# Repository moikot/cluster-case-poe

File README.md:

# A quiet case for three Raspberry Pis

* ✨Power over Ethernet
* ✨Hot-swap support 
* ✨PWM fans support
---

## Table of Contents

- [Enclosure](#enclosure)
  - [Power and I2C rail](#power-and-i2c-rail)
  - [Fan controller](#fan-controller)
  - [Bill of materials](#enclosure-bill-of-materials)
- [Frames](#frames)
  - [PoE assembly](#poe-assembly)
  - [Bill of materials](#frames-bill-of-materials)
- [Other hardware needed](#other-hardware-needed)
- [License](#license)

## Enclosure

The case box is built from the following parts ([drawings](drawings/cluster-box-drawings.pdf)):

* Left, right, top, and bottom panels.
* Top and bottom panels with grooves for the Raspberry Pi frames.
* A back panel with a fan grill for 80mm x 80mm fan.
* A front panel with openings for USB and Ethernet ports. 

> Watch this [video](https://youtu.be/zfYN2NjLpm8) to see how to assembly the case.

### Power and I2C rail

The power and I2C rail connects all Raspberry Pis to the I2C bus and provides power to the fan controller and a chassis fan. Low forward drop Schottky diodes combined in an OR-ing circuit provide power to the load when at least one Raspberry Pi is installed without the risk of reverse current flow. 

> * [Schematics and PCB (EagleCAD)](power-rail)
> * [BOM](power-rail/power-rail-bom.csv)

### Fan controller

The fan controller converts 5V to 12V and uses [EMC2101-R IC](https://www.microchip.com/wwwproducts/en/EMC2101) from Microchip/SMSC to control a 4-pin PWM fan and monitor its speed via the I2C bus. This controller is installed on the left panel of the enclosure and connected to the [Power and I2C rail](#power-and-i2c-rail).

> * [Schematics and PCB (EagleCAD)](fan-controller)
> * [BOM](fan-controller/fan-controller-bom.csv)

### Bill of materials

|        Part         | Quantity | Link |
|---------------------|----------|------|
| M2.5 x 14mm screw   | 3        | [M2.5 machine screws nuts kit](https://www.ebay.com/itm/182282169506)     |
| M2.5 x 10mm screw   | 1        | [M2.5 machine screws nuts kit](https://www.ebay.com/itm/182282169506)     |
| M2.5 nut            | 4        | [M2.5 machine screws nuts kit](https://www.ebay.com/itm/182282169506)     |
| M2.5 x 2mm spacer   | 4        | [M2.5 round plastic spacer](https://www.digikey.com/en/products/detail/w%C3%BCrth-elektronik/960020021/9488359)     |
| M3 x 12mm screw     | 8        | 	[M3x12mm machine screws](https://www.amazon.com/Uxcell-a15070200ux0058-Stainless-Phillips-Screws/dp/B012TE1TBS) |
| M3 nut              | 8        | [M3 hexagon nuts](https://www.amazon.com/uxcell-Metric-Stainless-Hexagon-Silver/dp/B07H3T4859) |
| M3 nylon washer     | 8        | [M3 nylon flat washers](https://www.amazon.com/uxcell-Insulation-Spacer-Washer-Gasket/dp/B016EPLM5G) |
| M4 x 14mm screw     | 4        | [M4x14mm machine screws](https://www.amazon.com/uxcell-M4x14mm-Phillips-Stainless-Fasteners/dp/B07MF44LGC) |
| M4 nut              | 4        | [M4 hexagon nuts](https://www.amazon.com/uxcell-Metric-Stainless-Hexagon-Silver/dp/B07H3VF3BF) |
| 80mm x 80mm x 25mm fan | 1        | [Noctua NF-A8 PWM](https://noctua.at/en/nf-a8-pwm) |
| Power and I2C rail | 1        | [Schematics and PCB (EagleCAD)](power-rail), [BOM](power-rail/power-rail-bom.csv) |
| Fan controller | 1        | [Schematics and PCB (EagleCAD)](fan-controller), [BOM](fan-controller/fan-controller-bom.csv) |
| Case panels | 8        | [Drawings](drawings/cluster-box-drawings.pdf), [Templates for laser cutting](drawings/cluster-box-laser-cut.pdf) |

## Frames

Raspberry Pis need to be mounted on frames so that they can be pushed into the case and retracted individually ([drawings](drawings/frame-drawings.pdf)).

### PoE assembly

The solution relies on a custom PoE HAT with [RT5400-5V 30W module](https://www.aliexpress.com/item/33038562052.html). For this HAT to work, the switch your cluster is connected to needs to support IEEE 802.3af Power over Ethernet protocol (e.g. [TL-SG1005P switch](https://www.tp-link.com/us/business-networking/poe-switch/tl-sg1005p/)). 

> * [Schematics and PCB (EagleCAD)](poe-assembly)
> * [BOM](poe-assembly/poe-assembly-bom.csv)

### Bill of materials
|        Part         | Quantity | Link |
|---------------------|----------|------|
| M2.5 x 10mm screw   | 12       | [M2.5 machine screws nuts kit](https://www.ebay.com/itm/182282169506)     |
| M2.5 x 5mm screw    | 6        | [M2.5 machine screws nuts kit](https://www.ebay.com/itm/182282169506)     |
| M2.5 nut            | 6        | [M2.5 machine screws nuts kit](https://www.ebay.com/itm/182282169506)     |
| M2.5 x 14mm F/F hex brass standoff | 6 | [Hex standoff M2.5 x 14mm brass](https://www.digikey.com/en/products/detail/harwin-inc/R25-1001402/3924434) |
| Raspberry Pi 4 Model B 4-8Gb | 3 | [Raspberry Pi 4](https://www.amazon.com/Uxcell-a15070200ux0058-Stainless-Phillips-Screws/dp/B012TE1TBS) | 
| Micro SD 32 Gb | 3 | [SanDisk Ultra 32GB](https://www.amazon.com/SanDisk-Ultra-UHS-I-Memory-Adapter/dp/B00M55C0NS) |
| PoE assembly | 3 | [Schematics and PCB (EagleCAD)](poe-assembly), [BOM](poe-assembly/poe-assembly-bom.csv) |
| Frame panels | 2 x 3 | [Drawings](drawings/frame-drawings.pdf), [Templates for laser cutting](drawings/frame-laser-cut.pdf) |

## Other hardware needed

* Three Ethernet patch cables 230-250mm length.
* A switch with 802.3af Power over Ethernet support (e.g. [TL-SG1005P switch](https://www.tp-link.com/us/business-networking/poe-switch/tl-sg1005p/)).

## License
This work is licensed under a Creative Commons Attribution-ShareAlike 4.0 International License, check [LICENSE](LICENSE) for more information.

You can support my work in the field of open-source hardware by clicking .

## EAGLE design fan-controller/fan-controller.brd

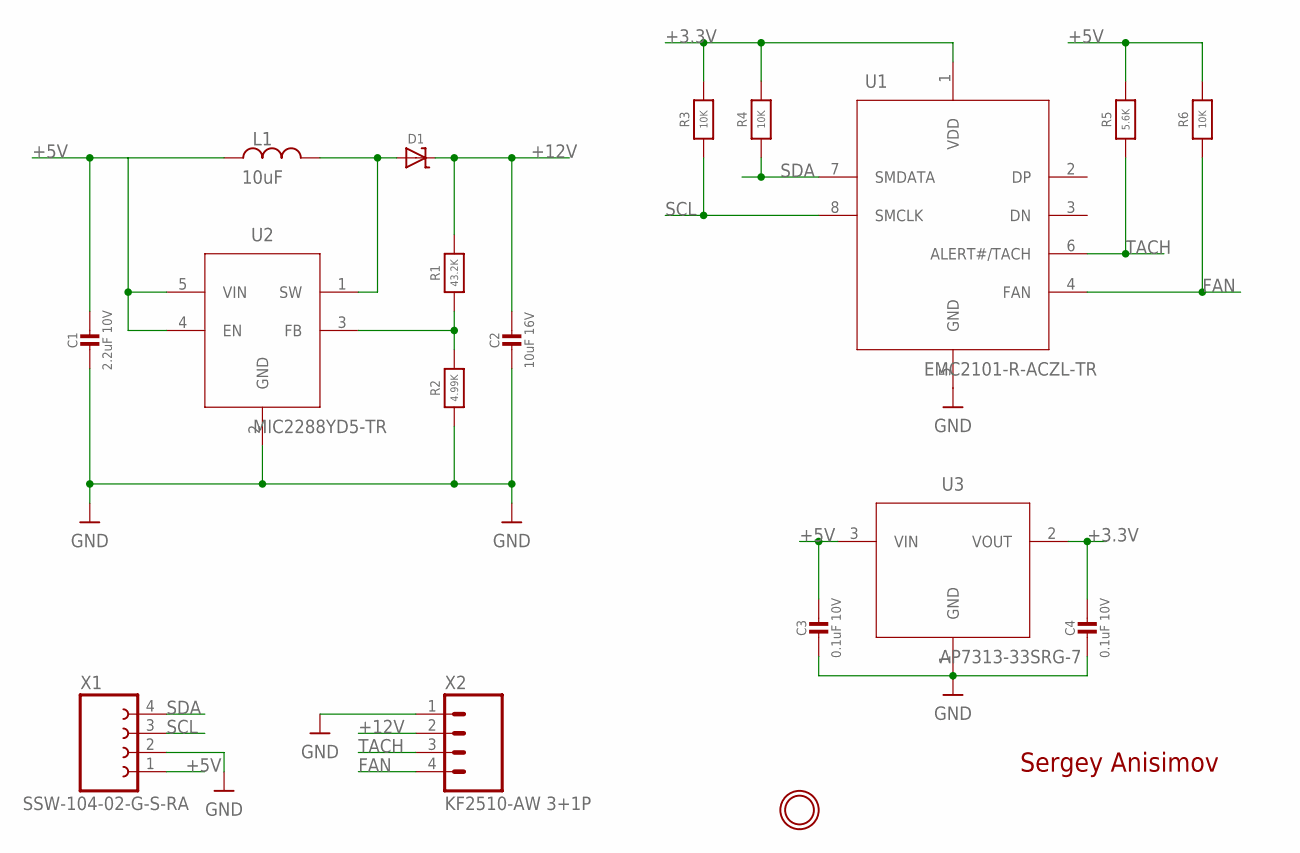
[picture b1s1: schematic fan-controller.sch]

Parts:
C1: 2.2uF 10V; CAPC1608X50N
C2: 10uF 16V; CAPC2012X139N
C3, C4: 0.1uF 10V; CAPC1205X55N
D1: DIODE-SCHOTTKY; CASE457−04
L1: 10uF; INDC3225X270
R1: 43.2K; RESC1608X55N
R2: 4.99K; RESC1608X55N
R3, R4, R6: 10K; RESC1005X40N
R5: 5.6K; RESC1005X40N
U1: EMC2101-R-ACZL-TR; SOP65P490X110-8N
U2: MIC2288YD5-TR; SOT95P279X100-5
U3: AP7313-33SRG-7; SOT95P240X120-3
U$7: MOUNTING-HOLE2.7_THICK; MOUNTINGHOLE_2.7_PLATED_THICK
X1: SSW-104-02-G-S-RA; HDRRAR4W64P254_1X4_1067X851X241B
X2: KF2510-AW 3+1P; HDRRA4W64P254_1X4_1016X300X580B

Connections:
+3.3V: C4.1, R3.2, R4.2, U1.1 (VDD), U3.2 (VOUT)
+5V: C1.1, C3.1, L1.1, R5.2, R6.2, U2.4 (EN), U2.5 (VIN), U3.3 (VIN), X1.1
+12V: C2.1, D1.C, R1.1, X2.2
FAN: R6.1, U1.4 (FAN), X2.4
GND: C1.2, C2.2, C3.2, C4.2, R2.1, U1.5 (GND), U2.2 (GND), U3.1 (GND), X1.2, X2.1
unnamed: D1.A, L1.2, U2.1 (SW)
unnamed: R1.2, R2.2, U2.3 (FB)
SCL: R3.1, U1.8 (SMCLK), X1.3
SDA: R4.1, U1.7 (SMDATA), X1.4
TACH: R5.1, U1.6 (ALERT#/TACH), X2.3

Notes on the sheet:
Sergey Anisimov

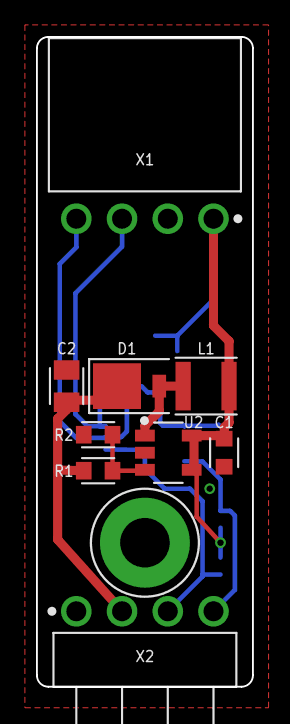
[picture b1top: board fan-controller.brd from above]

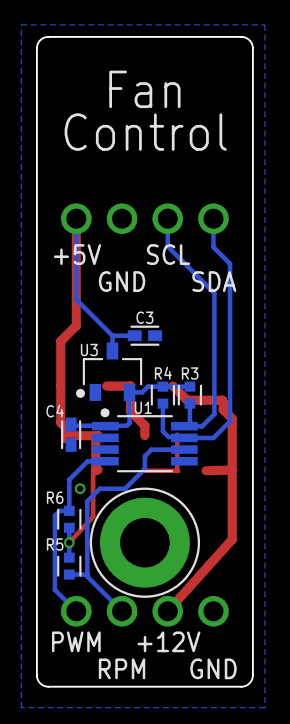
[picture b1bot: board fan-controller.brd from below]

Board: 2 copper layers, 12.0 x 36.1 mm, 18 parts (8 on the bottom side), 10 nets.

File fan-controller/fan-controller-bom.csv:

Designator,Name,Value,Amount,Case,Link
X1,Connector,SSW-104-02-G-S-RA,1,,https://no.mouser.com/ProductDetail/SSW-104-02-G-S-RA
X2,Connector,KF2510-AW 3+1P,1,,https://www.aliexpress.com/item/32961935772.html
C1,Capacitor,2.2uF 10V,1,0603,https://no.mouser.com/ProductDetail/187-CL10A225KP8NNNC
C2,Capacitor,10uF 16V,1,0805,https://no.mouser.com/ProductDetail/187-CL21A106KOQNNNE
"C3,C4",Capacitor,0.1uF 10V,2,0402_L,https://no.mouser.com/ProductDetail/187-CL05A104KP5NNWC
L1,Inductor,10uH,1,1210,https://no.mouser.com/ProductDetail/963-CBC3225T100KR
D1,Schottky Diode,,1,DO-216AA,https://no.mouser.com/ProductDetail/863-MBRM140T1G
R1,Resistor,43.2K,1,0603,https://no.mouser.com/ProductDetail/603-RC0603FR-0743K2L
R2,Resistor,4.99K,1,0603,https://no.mouser.com/ProductDetail/603-RC0603FR-074K99L
"R3,R4,R6",Resistor,10K,3,0402,https://no.mouser.com/ProductDetail/603-RC0402FR-0710KL
R5,Resistor,5.6K,1,0402,https://no.mouser.com/ProductDetail/603-AC0402FR-075K6L
U1,Voltage regulator,MIC2288YD5-TR,1,SOT-23-5,https://no.mouser.com/ProductDetail/998-MIC2288YD5TR
U2,Fan controller,EMC2101-R-ACZL-TR,1,MSOP-8,https://no.mouser.com/ProductDetail/886-EMC2101RACZLTR
U3,LDO 3.3V,AP7313-33SRG-7,1,SOT-23-3,https://no.mouser.com/ProductDetail/621-AP7313-33SRG-7

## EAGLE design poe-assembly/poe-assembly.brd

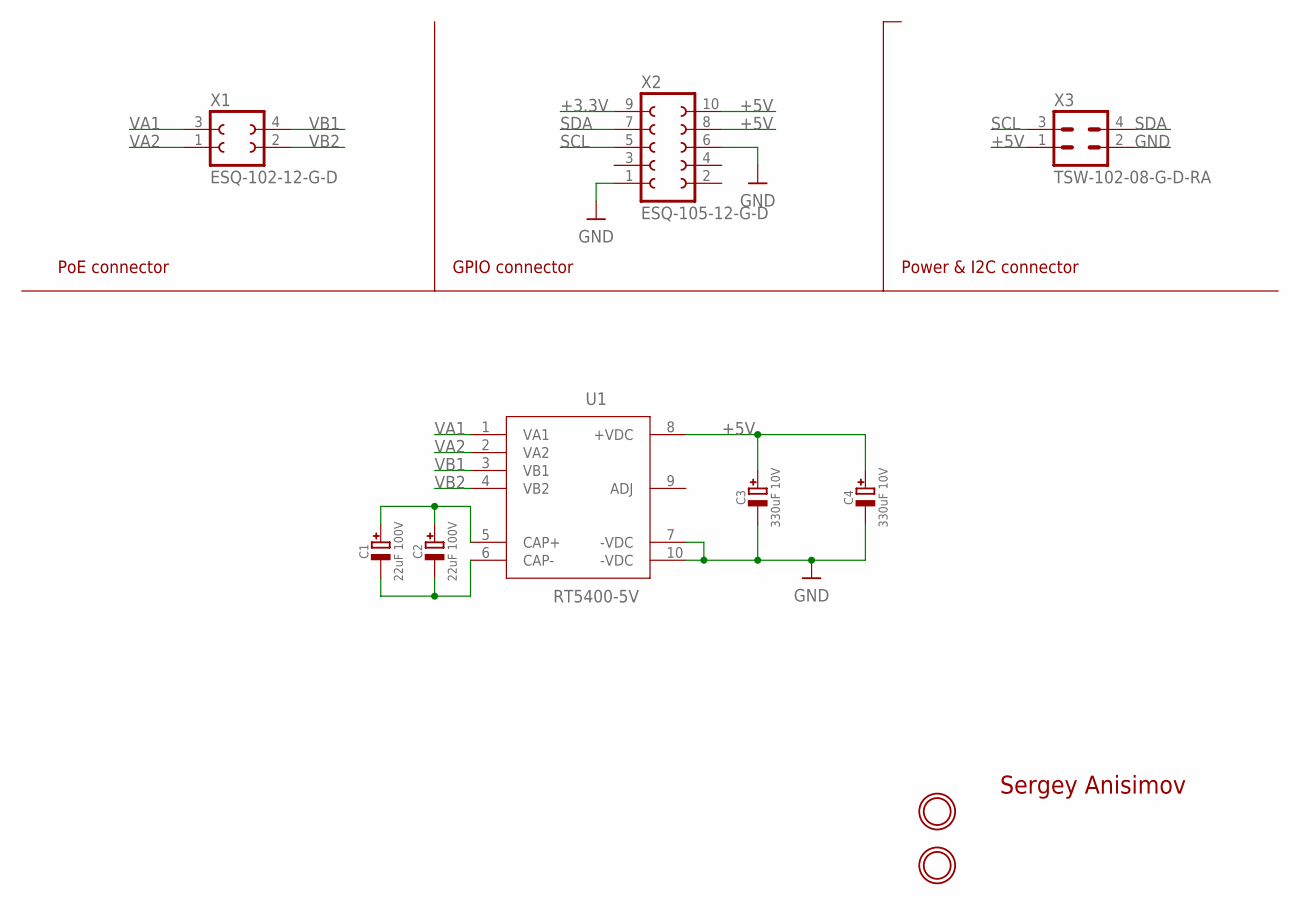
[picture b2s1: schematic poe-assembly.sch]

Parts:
C1, C2: 22uF 100V; CAP-PRD250-W50-D630
C3, C4: 330uF 10V; CAP-PRD250-W50-D630
U1: RT5400-5V; MODULE-RT5400
U$6, U$7: MOUNTING-HOLE2.7_THICK; MOUNTINGHOLE_2.7_PLATED_THICK
X1: ESQ-102-12-G-D; ESQ-102-D
X2: ESQ-105-12-G-D; ESQ-105-D
X3: TSW-102-08-G-D-RA; TSW-102-D-RA

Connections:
+3.3V: X2.9
+5V: C3.1 (+), C4.1 (+), U1.8 (+VDC), X2.8, X2.10, X3.1
GND: C3.2 (-), C4.2 (-), U1.7 (-VDC), U1.10 (-VDC), X2.1, X2.6, X3.2
unnamed: C1.1 (+), C2.1 (+), U1.5 (CAP+)
unnamed: C1.2 (-), C2.2 (-), U1.6 (CAP-)
SCL: X2.5, X3.3
SDA: X2.7, X3.4
VA1: U1.1 (VA1), X1.3
VA2: U1.2 (VA2), X1.1
VB1: U1.3 (VB1), X1.4
VB2: U1.4 (VB2), X1.2

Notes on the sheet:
Sergey Anisimov
PoE connector
GPIO connector
Power & I2C connector

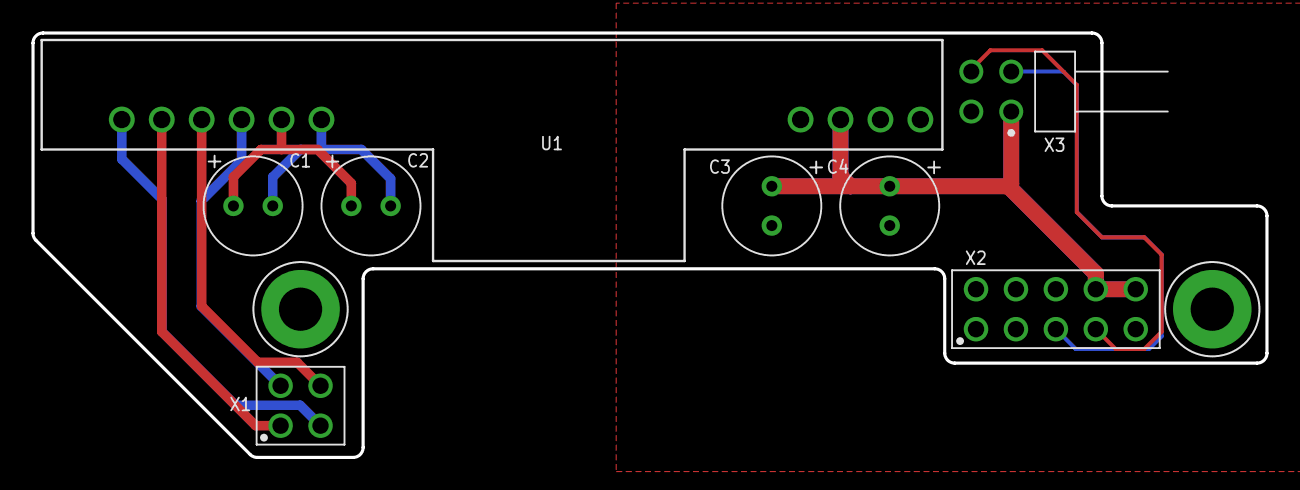
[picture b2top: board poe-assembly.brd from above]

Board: 2 copper layers, 78.5 x 27.0 mm, 10 parts (0 on the bottom side), 10 nets.

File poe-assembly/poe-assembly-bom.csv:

Designator,Name,Value,Amount,Case,Link
X1,Connector,ESQ-102-12-G-D,1,,https://no.mouser.com/ProductDetail/200-ESQ10212GD
X2,Connector,ESQ-105-12-G-D,1,,https://no.mouser.com/ProductDetail/200-ESQ10512GD
X3,Connector,TSW-102-08-G-D-RA,1,,https://no.mouser.com/ProductDetail/TSW-102-08-G-D-RA
"C1,C2",Capacitor,22uF 100V,2,,https://no.mouser.com/ProductDetail/667-ECA-2AM220I
"C3,C4",Capacitor,330uF 10V,2,,https://no.mouser.com/ProductDetail/667-EEU-FS1A331
RT5400,PoE module,RT5400 5V,1,,https://www.aliexpress.com/item/33038562052.html

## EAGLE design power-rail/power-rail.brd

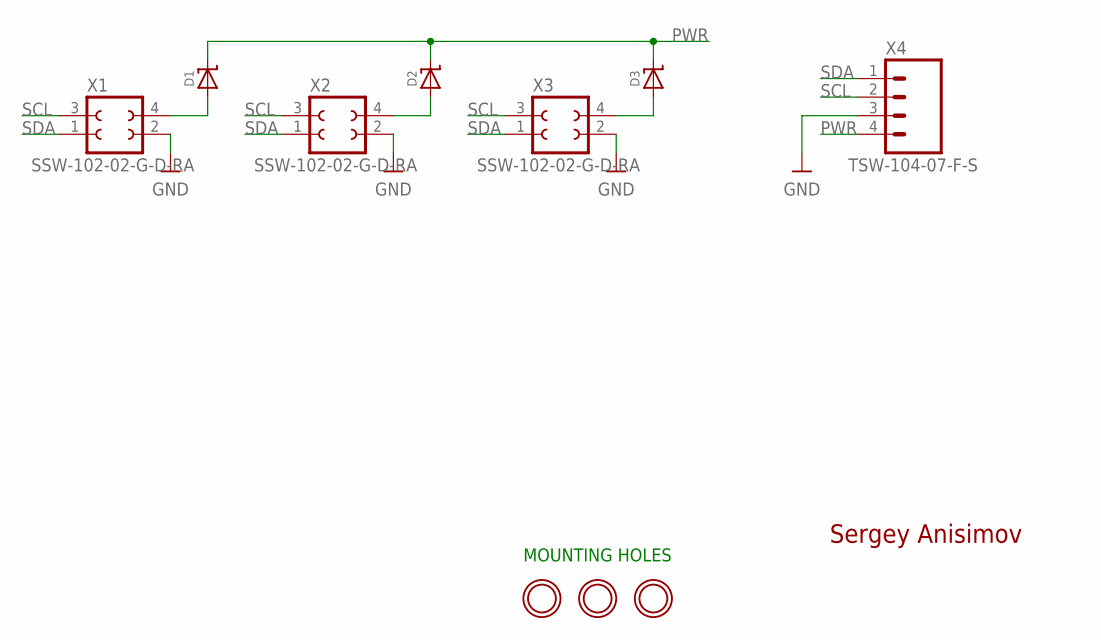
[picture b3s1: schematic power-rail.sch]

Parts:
D1, D2, D3: DIODE-SCHOTTKYSOD−123FL; SODFL3616X98
U$5, U$6, U$7: MOUNTING-HOLE2.7_THICK; MOUNTINGHOLE_2.7_PLATED_THICK
X1, X2, X3: SSW-102-02-G-D-RA; SSQ-102-02-T-D-RA
X4: TSW-104-07-F-S; HDRV4W64P254_1X4_1016X254X838B

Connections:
GND: X1.2, X2.2, X3.2, X4.3
unnamed: D1.A, X1.4
unnamed: D2.A, X2.4
unnamed: D3.A, X3.4
PWR: D1.C, D2.C, D3.C, X4.4
SCL: X1.3, X2.3, X3.3, X4.2
SDA: X1.1, X2.1, X3.1, X4.1

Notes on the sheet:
MOUNTING HOLES
Sergey Anisimov

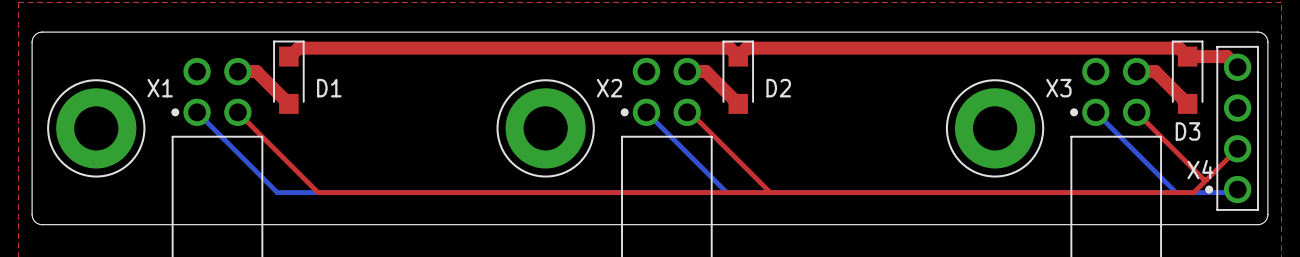
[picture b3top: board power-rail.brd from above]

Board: 2 copper layers, 77.0 x 12.0 mm, 10 parts (0 on the bottom side), 7 nets.

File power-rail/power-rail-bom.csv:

Designator,Name,Value,Amount,Case,Link
"X1,X2,X3",Connector,SSW-102-02-G-D-RA,3,,https://no.mouser.com/ProductDetail/SSW-102-02-G-D-RA
X4,Connector,TSW-104-07-F-S,1,,https://no.mouser.com/ProductDetail/200-TSW10407FS
"D1,D2,D2",Schottky Diode,RB161MM-20TR,3,,https://no.mouser.com/ProductDetail/755-RB161MM-20TR
